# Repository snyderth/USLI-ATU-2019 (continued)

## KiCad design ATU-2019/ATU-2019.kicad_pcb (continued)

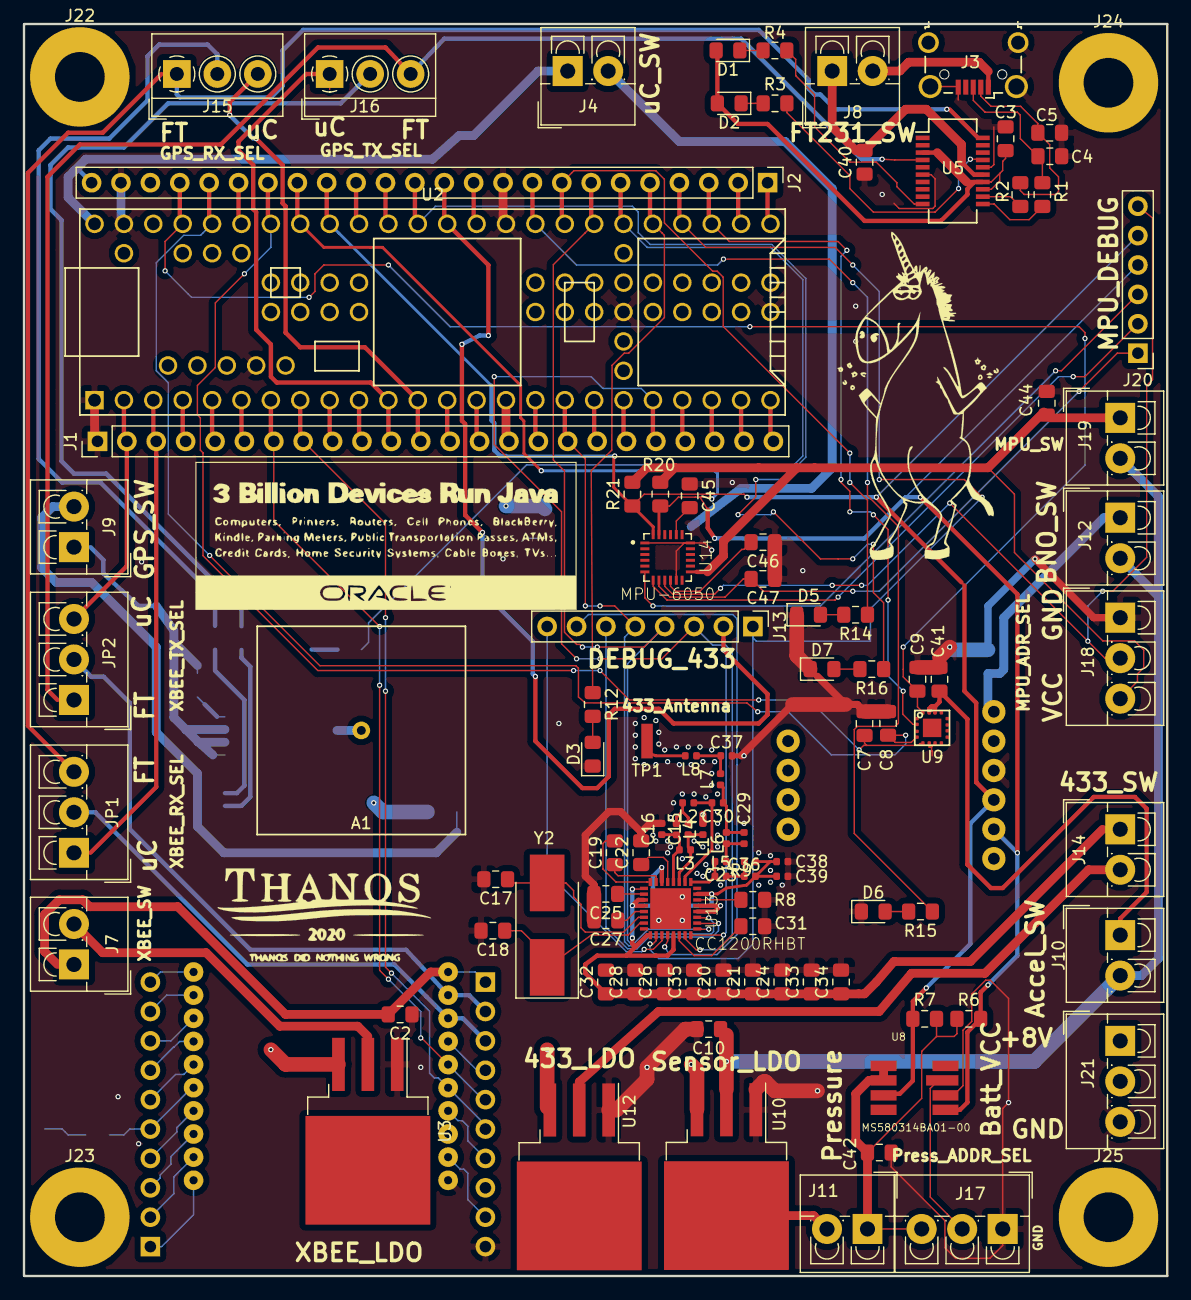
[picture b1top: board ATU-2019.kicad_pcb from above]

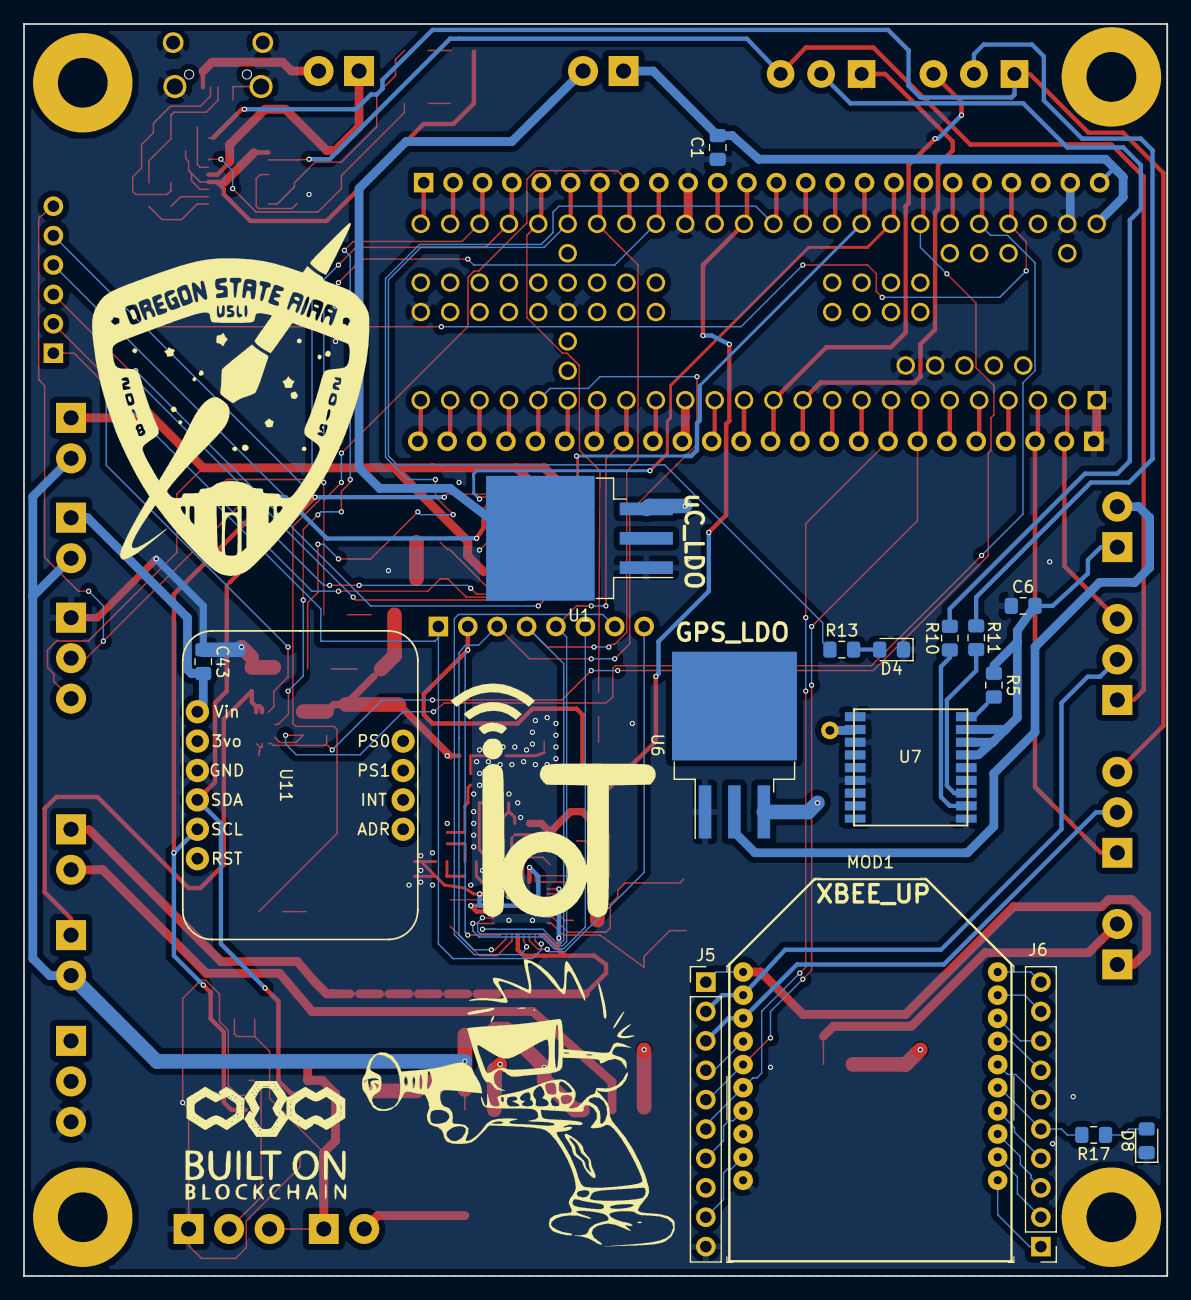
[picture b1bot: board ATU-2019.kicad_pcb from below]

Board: 4 copper layers, 98.8 x 108.2 mm, 122 parts (17 on the bottom side), 127 nets.

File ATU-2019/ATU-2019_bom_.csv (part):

Component,Description,Part,References,Value,Footprint,Quantity Per PCB,Datasheet,Field4,Field5,Field6,Field7,Field8
1,b'',b'ANTENNA',b'A1 A2',b'ANTENNA',b'Patch_Antenna_18mmx18mm',b'2',b'',b'',b'',b'',b'',b''
2,b'Unpolarized capacitor',b'C',b'C3 C7 C8 C9 C13',b'0.1uF',b'C_0805_2012Metric_Pad1.15x1.40mm_HandSolder',b'5',b'~',b'',b'',b'',b'',b''
3,"b'Unpolarized capacitor, small symbol'",b'C_Small',b'C19',b'1.5nF',b'C_0805_2012Metric_Pad1.15x1.40mm_HandSolder',b'1',b'~',b'',b'',b'',b'',b''
4,b'Unpolarized capacitor',b'C',b'C39',b'100pF',b'C_0805_2012Metric_Pad1.15x1.40mm_HandSolder',b'1',b'~',b'',b'',b'',b'',b''
5,b'Unpolarized capacitor',b'C',b'C27 C38',b'10nF',b'C_0805_2012Metric_Pad1.15x1.40mm_HandSolder',b'2',b'~',b'',b'',b'',b'',b''
6,b'Unpolarized capacitor',b'C',b'C17 C18',b'15pF',b'C_0805_2012Metric_Pad1.15x1.40mm_HandSolder',b'2',b'~',b'',b'',b'',b'',b''
7,b'Unpolarized capacitor',b'C',b'C29',b'2.2pF',b'C_0805_2012Metric_Pad1.15x1.40mm_HandSolder',b'1',b'~',b'',b'',b'',b'',b''
8,b'Unpolarized capacitor',b'C',b'C31',b'220nF',b'C_0805_2012Metric_Pad1.15x1.40mm_HandSolder',b'1',b'~',b'',b'',b'',b'',b''
9,b'Unpolarized capacitor',b'C',b'C11 C12',b'22pF',b'C_0805_2012Metric_Pad1.15x1.40mm_HandSolder',b'2',b'~',b'',b'',b'',b'',b''
10,b'Unpolarized capacitor',b'C',b'C23',b'39pF',b'C_0805_2012Metric_Pad1.15x1.40mm_HandSolder',b'1',b'~',b'',b'',b'',b'',b''
11,b'Unpolarized capacitor',b'C',b'C1 C2 C6 C10 C14 C40 C41 C42 C43',b'4700pF',b'C_0805_2012Metric_Pad1.15x1.40mm_HandSolder',b'9',b'~',b'',b'',b'',b'',b''
12,b'Unpolarized capacitor',b'C',b'C20 C21 C22 C24 C25 C26 C28 C32 C33 C34 C35',b'47nF',b'C_0805_2012Metric_Pad1.15x1.40mm_HandSolder',b'11',b'~',b'',b'',b'',b'',b''
13,b'Unpolarized capacitor',b'C',b'C4 C5',b'47pF',b'C_0805_2012Metric_Pad1.15x1.40mm_HandSolder',b'2',b'~',b'',b'',b'',b'',b''
14,b'Unpolarized capacitor',b'C',b'C15 C16 C30',b'5.1pF',b'C_0805_2012Metric_Pad1.15x1.40mm_HandSolder',b'3',b'~',b'',b'',b'',b'',b''
15,b'Unpolarized capacitor',b'C',b'C36',b'56pF',b'C_0805_2012Metric_Pad1.15x1.40mm_HandSolder',b'1',b'~',b'',b'',b'',b'',b''
16,b'Unpolarized capacitor',b'C',b'C37',b'6.2pF',b'C_0805_2012Metric_Pad1.15x1.40mm_HandSolder',b'1',b'~',b'',b'',b'',b'',b''
17,b'Light emitting diode',b'LED',b'D3',b'433_Heartbeat',b'LED_0805_2012Metric_Pad1.15x1.40mm_HandSolder',b'1',b'~',b'',b'',b'',b'',b''
18,b'Light emitting diode',b'LED',b'D7',b'ACCEL_heartbeat',b'LED_0805_2012Metric_Pad1.15x1.40mm_HandSolder',b'1',b'~',b'',b'',b'',b'',b''
19,b'Light emitting diode',b'LED',b'D4',b'GPS_Heartbeat',b'LED_0805_2012Metric_Pad1.15x1.40mm_HandSolder',b'1',b'~',b'',b'',b'',b'',b''
20,b'Light emitting diode',b'LED',b'D5',b'IMU_heartbeat',b'LED_0805_2012Metric_Pad1.15x1.40mm_HandSolder',b'1',b'~',b'',b'',b'',b'',b''
21,b'Light emitting diode',b'LED',b'D6',b'MS0_heartbeat',b'LED_0805_2012Metric_Pad1.15x1.40mm_HandSolder',b'1',b'~',b'',b'',b'',b'',b''
22,b'Light emitting diode',b'LED',b'D2',b'Red',b'LED_0805_2012Metric_Pad1.15x1.40mm_HandSolder',b'1',b'~',b'',b'',b'',b'',b''
23,b'Light emitting diode',b'LED',b'D8',b'XBEE_HEARTBEAT',b'LED_0805_2012Metric_Pad1.15x1.40mm_HandSolder',b'1',b'~',b'',b'',b'',b'',b''
24,b'Light emitting diode',b'LED',b'D1',b'Yellow',b'LED_0805_2012Metric_Pad1.15x1.40mm_HandSolder',b'1',b'~',b'',b'',b'',b'',b''
25,"b'Generic connector, single row, 01x02, script generated (kicad-library-utils/schlib/autogen/connector/)'",b'Conn_01x02_Male',b'J10',b'ACCEL_SW',b'PinHeader_1x02_P2.54mm_Vertical',b'1',b'~',b'',b'',b'',b'',b''
26,"b'Generic connector, single row, 01x08, script generated (kicad-library-utils/schlib/autogen/connector/)'",b'Conn_01x08_Female',b'J13',b'DEBUG_BREAKOUT_433',b'PinHeader_1x08_P2.54mm_Vertical',b'1',b'~',b'',b'',b'',b'',b''
27,b'USB Micro Type B connector',b'USB_B_Micro',b'J3',b'FT231X_USB',b'USB_Micro-B_Wuerth_629105150521_CircularHoles',b'1',b'~',b'',b'',b'',b'',b''
28,"b'Generic connector, single row, 01x02, script generated (kicad-library-utils/schlib/autogen/connector/)'",b'Conn_01x02_Male',b'J8',b'FT231_SW',b'PinHeader_1x02_P2.54mm_Vertical',b'1',b'~',b'',b'',b'',b'',b''
29,"b'Generic connector, single row, 01x02, script generated (kicad-library-utils/schlib/autogen/connector/)'",b'Conn_01x02_Male',b'J9',b'GPS_SW',b'PinHeader_1x02_P2.54mm_Vertical',b'1',b'~',b'',b'',b'',b'',b''
30,"b'Generic connector, single row, 01x02, script generated (kicad-library-utils/schlib/autogen/connector/)'",b'Conn_01x02_Male',b'J12',b'IMU_SW',b'PinHeader_1x02_P2.54mm_Vertical',b'1',b'~',b'',b'',b'',b'',b''
31,"b'Generic connector, single row, 01x02, script generated (kicad-library-utils/schlib/autogen/connector/)'",b'Conn_01x02_Male',b'J11',b'PRESSURE_SW',b'PinHeader_1x02_P2.54mm_Vertical',b'1',b'~',b'',b'',b'',b'',b''
32,"b'Generic connector, single row, 01x02, script generated (kicad-library-utils/schlib/autogen/connector/)'",b'Conn_01x02_Male',b'J4',b'TEENSY_SW',b'PinHeader_1x02_P2.54mm_Vertical',b'1',b'~',b'',b'',b'',b'',b''
33,"b'Generic connector, single row, 01x24, script generated (kicad-library-utils/schlib/autogen/connector/)'",b'Conn_01x24_Female',b'J1',b'Teensy_LHS',b'PinHeader_1x24_P2.54mm_Vertical',b'1',b'~',b'',b'',b'',b'',b''
34,"b'Generic connector, single row, 01x24, script generated (kicad-library-utils/schlib/autogen/connector/)'",b'Conn_01x24_Female',b'J2',b'Teensy_RHS',b'PinHeader_1x24_P2.54mm_Vertical',b'1',b'~',b'',b'',b'',b'',b''
35,"b'Generic connector, single row, 01x10, script generated (kicad-library-utils/schlib/autogen/connector/)'",b'Conn_01x10_Male',b'J5',b'XBEE_LHS',b'PinHeader_1x10_P2.54mm_Vertical',b'1',b'~',b'',b'',b'',b'',b''
36,"b'Generic connector, single row, 01x10, script generated (kicad-library-utils/schlib/autogen/connector/)'",b'Conn_01x10_Male',b'J6',b'XBEE_RHS',b'PinHeader_1x10_P2.54mm_Vertical',b'1',b'~',b'',b'',b'',b'',b''
37,"b'Generic connector, single row, 01x02, script generated (kicad-library-utils/schlib/autogen/connector/)'",b'Conn_01x02_Male',b'J7',b'XBEE_SW',b'PinHeader_1x02_P2.54mm_Vertical',b'1',b'~',b'',b'',b'',b'',b''
38,"b'Dual jumper, normally closed'",b'Jumper_NC_Dual',b'JP3',b'GPS_RX_JUMPER',b'FanPinHeader_1x03_P2.54mm_Vertical',b'1',b'~',b'',b'',b'',b'',b''
39,"b'Dual jumper, normally closed'",b'Jumper_NC_Dual',b'JP4',b'GPS_TX_JUMPER',b'FanPinHeader_1x03_P2.54mm_Vertical',b'1',b'~',b'',b'',b'',b'',b''
40,"b'Dual jumper, normally closed'",b'Jumper_NC_Dual',b'JP5',b'I2C_ADDR',b'FanPinHeader_1x03_P2.54mm_Vertical',b'1',b'~',b'',b'',b'',b'',b''
41,"b'Dual jumper, normally closed'",b'Jumper_NC_Dual',b'JP1',b'XBEE_RX_JUMPER',b'FanPinHeader_1x03_P2.54mm_Vertical',b'1',b'~',b'',b'',b'',b'',b''
42,"b'Dual jumper, normally closed'",b'Jumper_NC_Dual',b'JP2',b'XBEE_TX_JUMPER',b'FanPinHeader_1x03_P2.54mm_Vertical',b'1',b'~',b'',b'',b'',b'',b''
43,b'',b'INDUCTOR-',b'L2',b'15nH',b'L_0402_1005Metric',b'1',b'',b'',b'',b'',b'',b''
44,b'Capacitor symbol for simulation only',b'INDUCTOR',b'L6',b'15nH',b'L_0402_1005Metric',b'1',b'~',b'',b'',b'',b'',b''
45,b'Capacitor symbol for simulation only',b'INDUCTOR',b'L8',b'22nH',b'L_0402_1005Metric',b'1',b'~',b'',b'',b'',b'',b''
46,b'',b'INDUCTOR-',b'L1 L4',b'27nH',b'L_0402_1005Metric',b'2',b'',b'',b'',b'',b'',b''
47,b'Capacitor symbol for simulation only',b'INDUCTOR',b'L7',b'43nH',b'L_0402_1005Metric',b'1',b'~',b'',b'',b'',b'',b''
48,b'',b'INDUCTOR-',b'L3',b'56nH',b'L_0402_1005Metric',b'1',b'',b'',b'',b'',b'',b''
49,b'Capacitor symbol for simulation only',b'INDUCTOR',b'L5',b'56nH',b'L_0402_1005Metric',b'1',b'~',b'',b'',b'',b'',b''
50,"b'Resistor, US symbol'",b'R_US',b'R18 R19',b'10k',b'R_0805_2012Metric_Pad1.15x1.40mm_HandSolder',b'2',b'~',b'',b'',b'',b'',b''
51,"b'Resistor, US symbol'",b'R_US',b'R9',b'18',b'R_0805_2012Metric_Pad1.15x1.40mm_HandSolder',b'1',b'~',b'',b'',b'',b'',b''
52,"b'Resistor, US symbol'",b'R_US',b'R3 R4 R12 R13 R14 R15 R16 R17',b'1k',b'R_0805_2012Metric_Pad1.15x1.40mm_HandSolder',b'8',b'~',b'',b'',b'',b'',b''
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
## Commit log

2018-11-05 add readme
2018-11-05 Finished schematic of FT231
2018-11-05 added .gitignore
2018-11-06 added teensy footprints and lib
2018-11-06 Moved blocks into seperate sheets, annotated teensy
2018-11-06 backing up to see if I can import GPS sch
2018-11-06 ignoring eagle to kicad converter
2018-11-06 Converted sparkfun eagle to kicad and added gps symbol to sch
2018-11-06 converted gps eagle files to kicad
2018-11-09 Finsihed sensors, still need GPS, finish PA on 433
2018-11-09 Need to add TX/RX jumpers for prog and associate footprints to symbols
2018-11-12 added todo, created and associated footprints
2018-11-17 Finished schematic
2018-11-17 Added xbee pinout reference
2018-11-19 finished TODO on schematic, need design review and will start on layout
2018-11-20 update added TODOs after design review
2018-11-20 Added MPU and moved BNO
2018-11-20 cleaning up IMU dir
2018-11-22 beginning on layout, fixed some issues with xbee footprint, added new IMU and migrated ada breakout in
2018-11-22 Initial layout done, connections need to be made
2018-11-22 Consolidating layout for miniturization
2018-11-25 Last commit before traces
2018-11-25 Final commit before traces
2018-12-08 changes from joint design check meeting
2018-12-14 Began running traces
2018-12-15 Finishing up connections on board, need to figure out the different for ground and +8v
2018-12-16 Done with layout, just need to double check all connections
2018-12-24 Finished the PCB and all graphics. Need to export the gerbers and check if this will work on OSHpark's website
2018-12-24 deleted moved the patch image
2019-02-05 Update deisgns
2019-02-05 Adding pdfs of layout
